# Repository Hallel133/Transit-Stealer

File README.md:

# Transit Stealer — V2

Open-hardware platform for **authorized NFC/RFID transit-card security research**: reading, analyzing, and interacting with transit fare cards for the purpose of testing and improving their security. This is not intended for, and must not be used for, unauthorized card cloning, skimming, or fare evasion.

## Board overview

V2 is a two-processor board:

- **RK3566** — main SoC (Cortex-A55 quad-core), running the host-side application. Referenced across three sheets since its pins are grouped by function (power, storage, RAM).
- **STM32G0B1CEUx** — dedicated MCU driving the NFC front end, largely independent of the RK3566 (own USB-C, own power sequencing), sharing only power/ground and a communication link with the rest of the board.
- **ST25R3911B-AQW** — NFC reader/writer IC, driven by the STM32G0 over SPI, feeding a custom hand-wound PCB loop antenna (see `Docs/Custom_Antenna.png`).
- **RK817-5 PMIC** — USB-C power in, battery charge/protection, all board rails (3.3V / 1.8V / DDR / CPU / GPU-NPU).
- **KLM8G1GETF-B041** eMMC and **D0811PM2FDGUK-U** LPDDR4 for RK3566 storage/RAM.
- **RTL8723BS** — WiFi/BT module (SDIO + UART).

Schematic is fully wired and ERC-clean (0 errors) as of this upload; PCB layout has not started.

## Repository layout

```
Hardware/
  Schematic/      V2 project + all hierarchical sheets (.kicad_sch/.kicad_pro/.kicad_prl), sym-lib-table
  PCB/            V2.kicad_pcb (layout, currently minimal/near-empty)
  Libraries/      Symbol libraries referenced by the schematic (bundled here so the project is self-contained)
Firmware/
  STM32G0_NFC_MCU/  Firmware for the NFC-side MCU (not started)
  RK3566_Host/      Host-side code for the RK3566 (not started)
Docs/
  Custom_Antenna.png  Hand-wound PCB loop antenna reference drawing
```

## Opening the project

1. Open `Hardware/Schematic/V2.kicad_pro` in KiCad 9.0.
2. The symbol libraries used by the LCD and eMMC parts live in `Hardware/Libraries/` and are referenced by `Hardware/Schematic/sym-lib-table` via relative (`${KIPRJMOD}`-based) paths, so the project should resolve them without any local path edits.
3. Run ERC (`kicad-cli sch erc` or the KiCad GUI) after any schematic change — sheets share nets, so the hierarchy is checked as one flat netlist.

## Status / next steps

- [x] Schematic: full net connectivity pass, power tree, decoupling, differential pairs verified
- [ ] PCB layout
- [ ] STM32G0 ↔ RK3566 communication firmware (next phase)

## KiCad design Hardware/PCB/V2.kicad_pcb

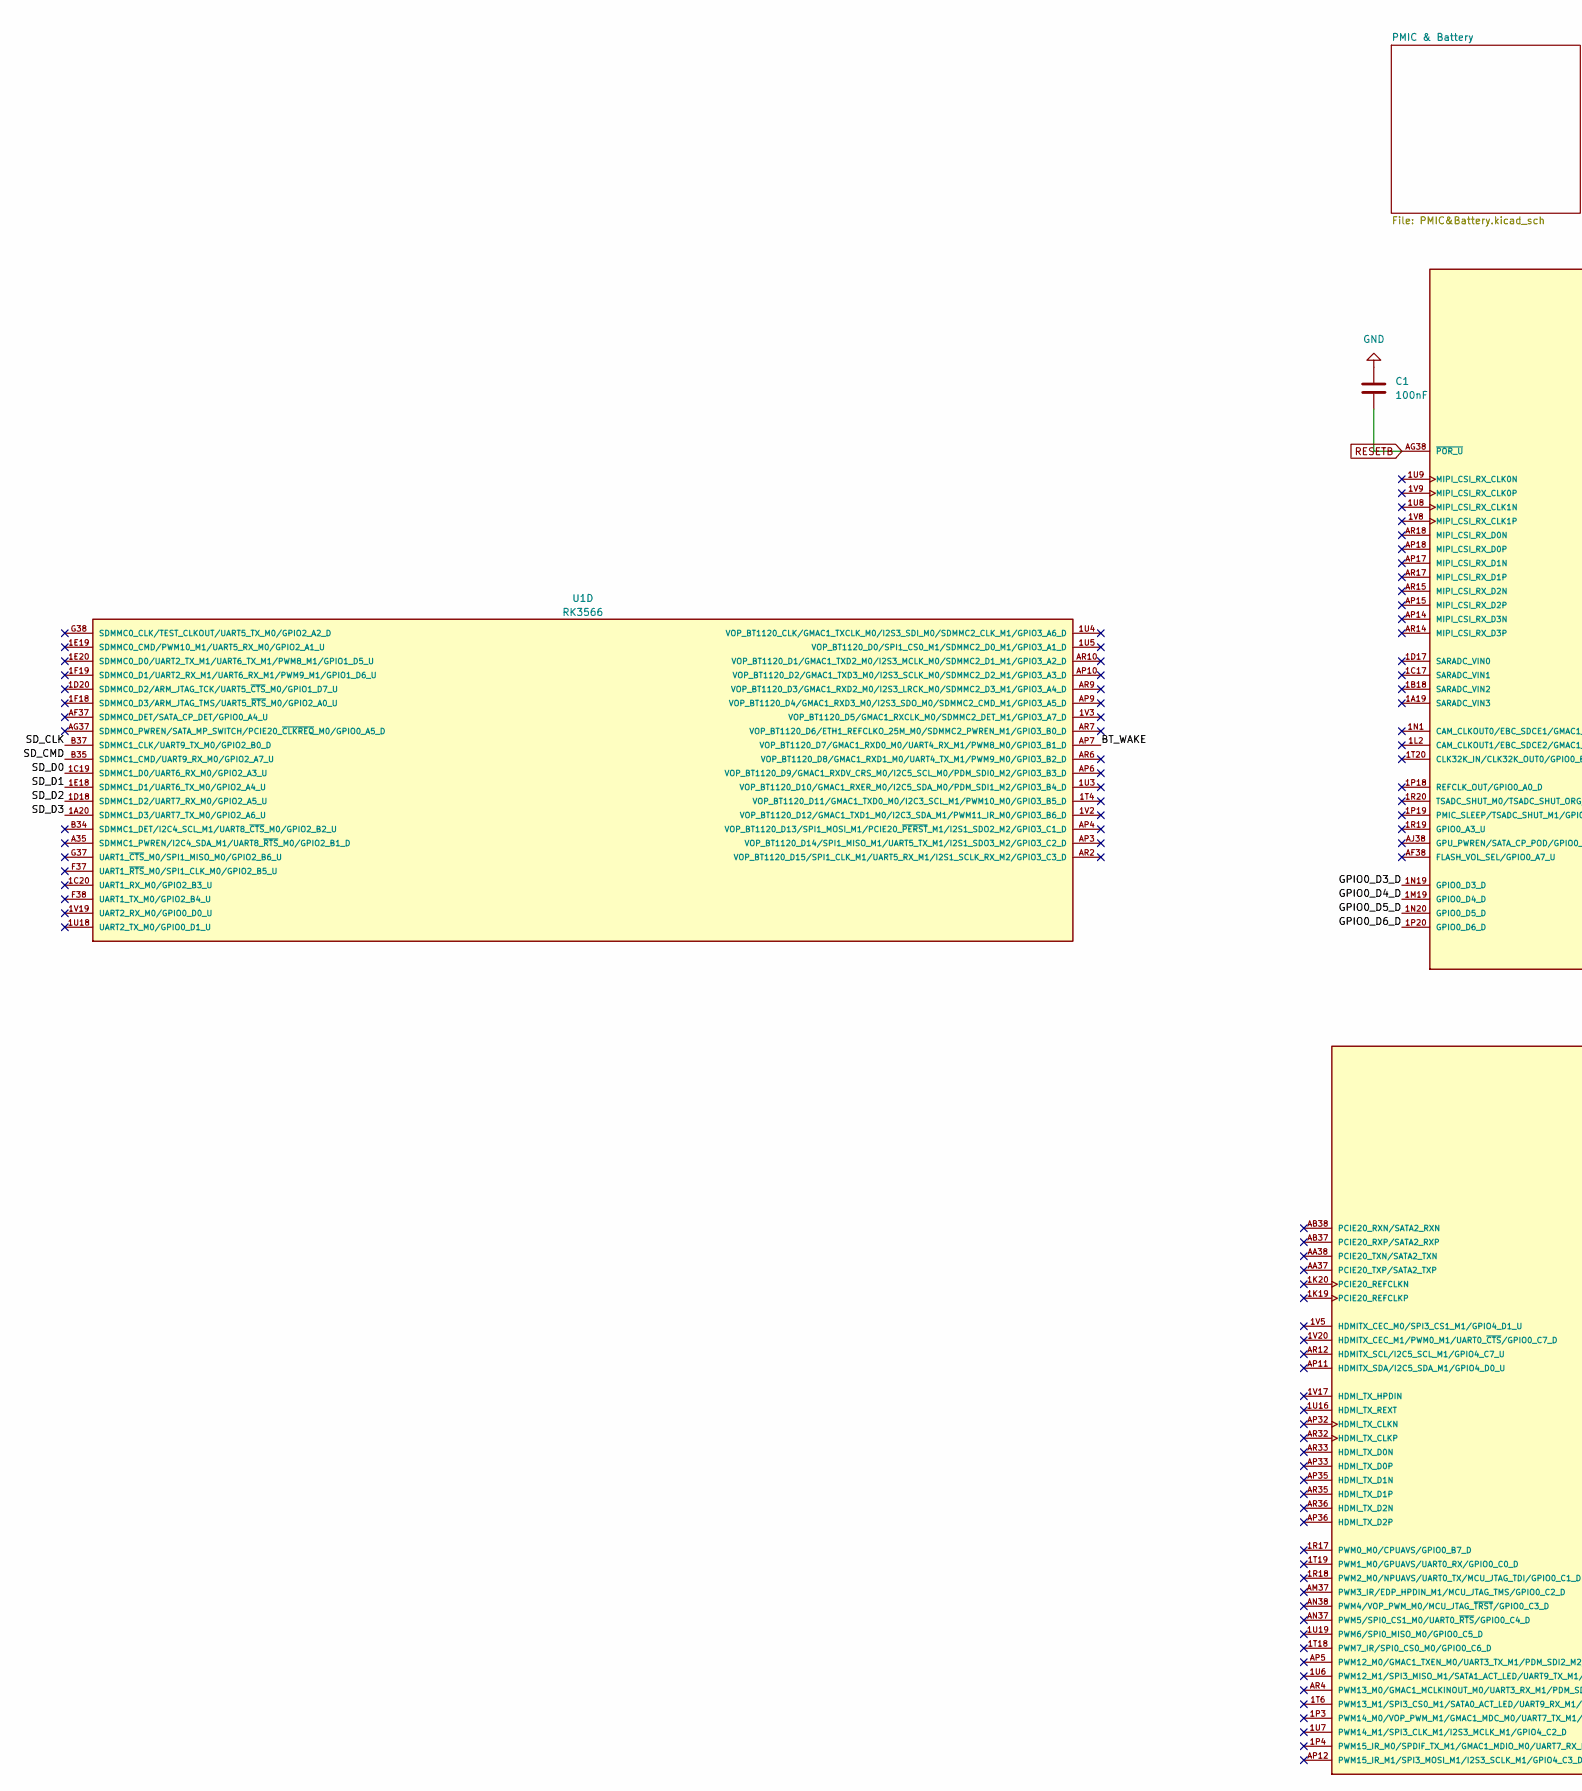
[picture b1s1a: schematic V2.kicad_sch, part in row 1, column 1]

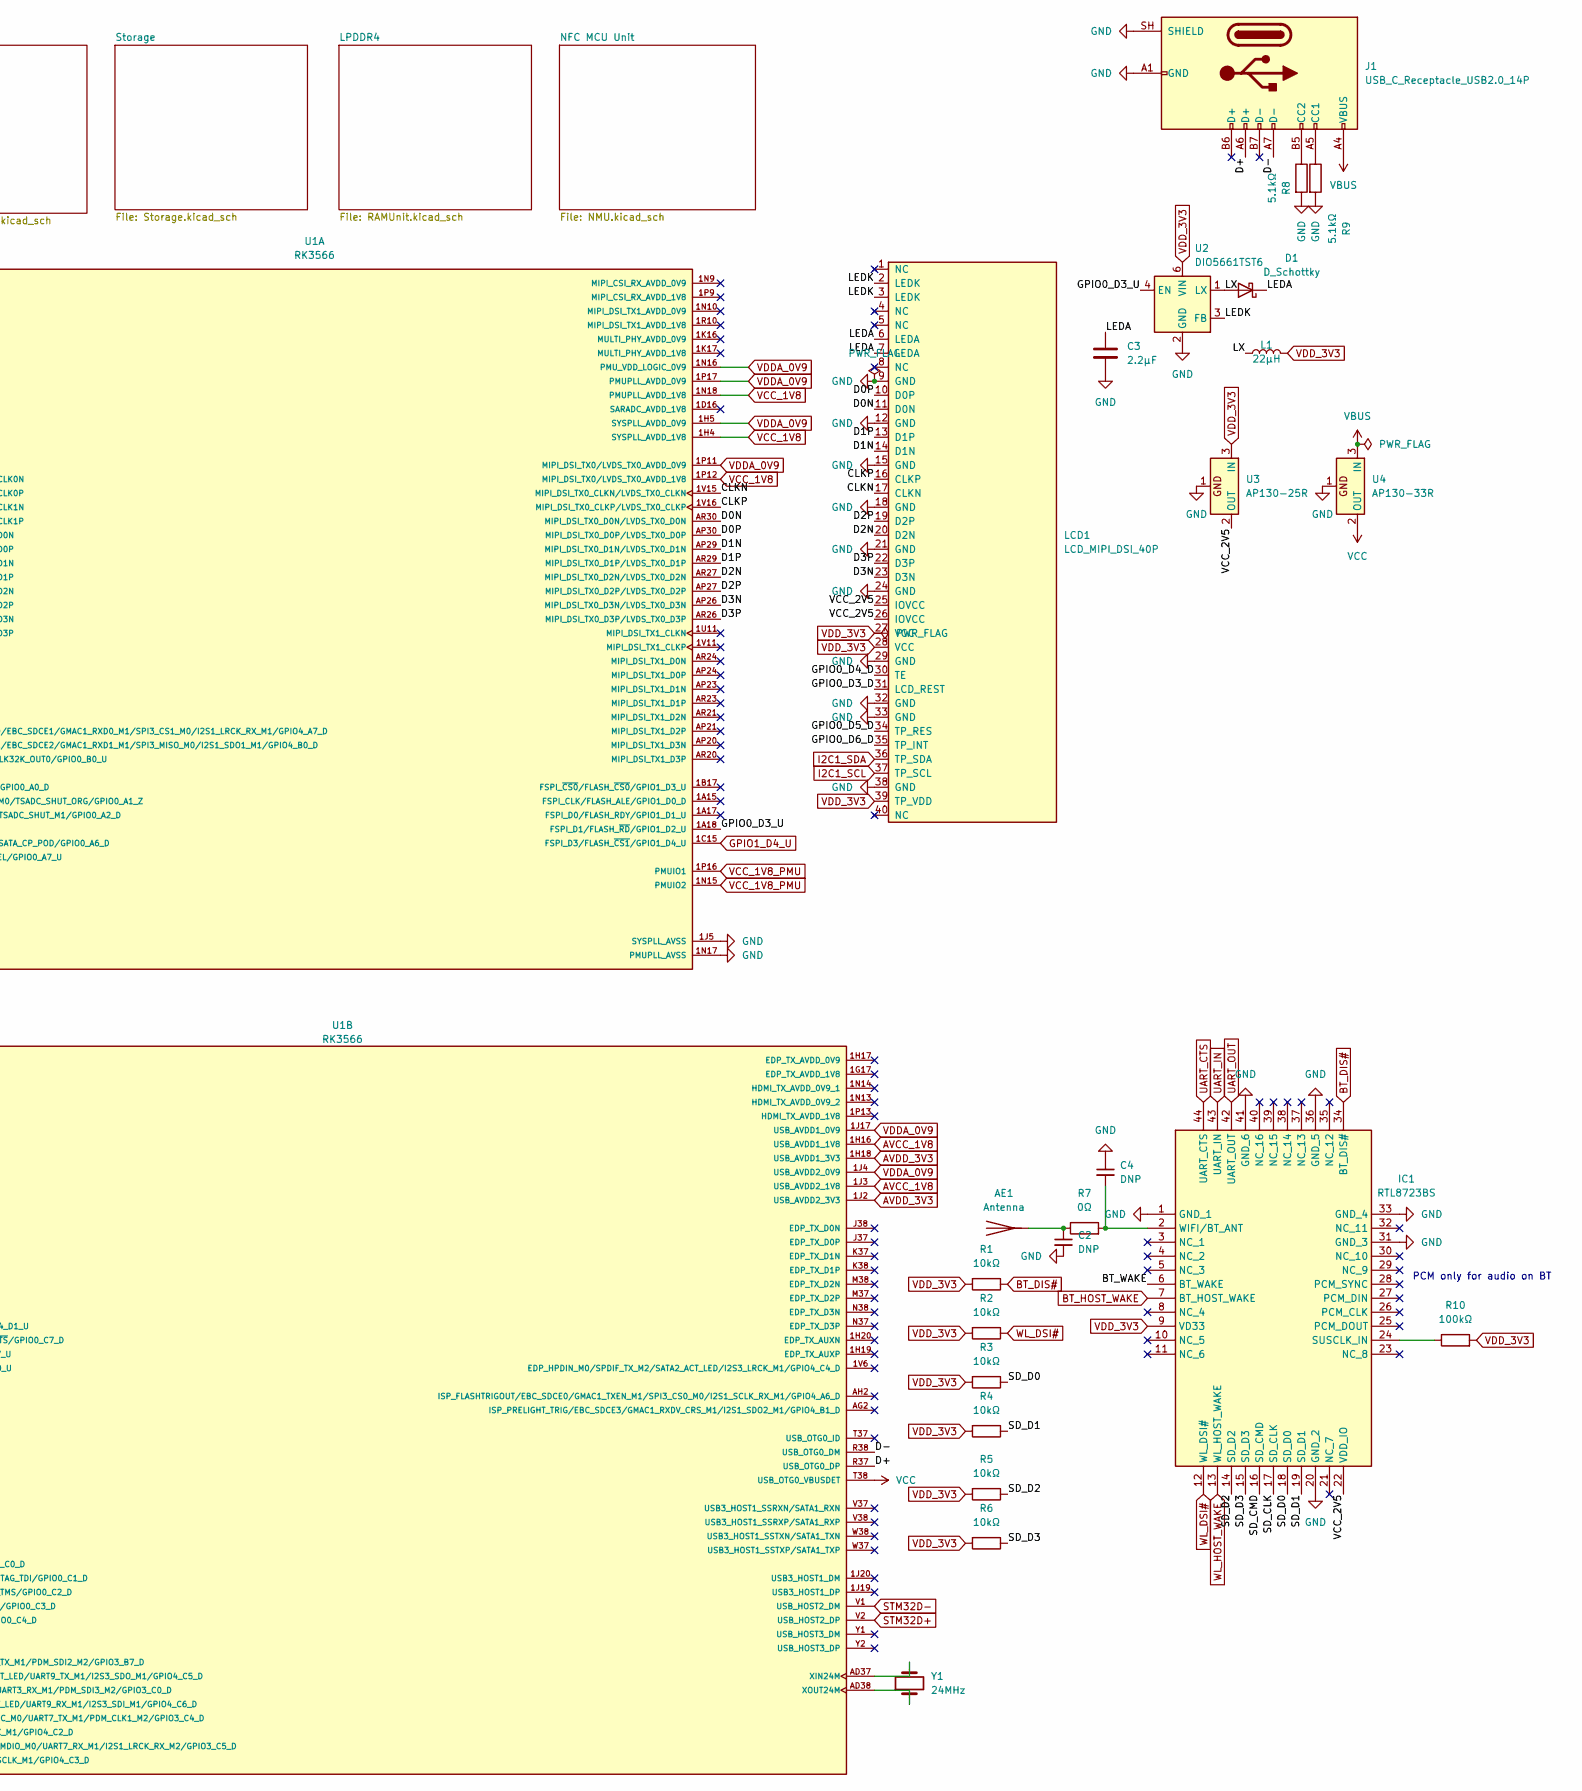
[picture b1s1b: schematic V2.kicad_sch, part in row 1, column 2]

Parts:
AE1: Antenna; Johanson_2450AT18x100
C1: 100nF; C_0402_1005Metric
C2, C4: DNP; C_0402_1005Metric
C3: 2.2µF; C_0402_1005Metric
D1: D_Schottky; D_SOD-123
IC1: RTL8723BS; Manufacturer_Part_Number RTL8723BS
J1: USB_C_Receptacle_USB2.0_14P; USB_C_Receptacle_GCT_USB4105-xx-A_16P_TopMnt_Horizontal
L1: 22µH; L_APV_ANR3010
LCD1: LCD_MIPI_DSI_40P; Amphenol_F32R-1A7x1-11040_1x40-1MP_P0.5mm_Horizontal
R1, R2, R3, R4, R5, R6: 10kΩ; R_0402_1005Metric
R7: 0Ω; R_0402_1005Metric
R8, R9: 5.1kΩ; R_0402_1005Metric
R10: 100kΩ; R_0402_1005Metric
U1: RK3566; PARTREV 1.1
U2: DIO5661TST6; TSOT-23-6
U3: AP130-25R; SC-59
U4: AP130-33R; SC-59
Y1: 24MHz; Crystal_SMD_3225-4Pin_3.2x2.5mm

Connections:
/BT_WAKE: IC1.6 (BT_WAKE), U1.AP7 (VOP_BT1120_D7/GMAC1_RXD0_M0/UART4_RX_M1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)
/CLKN: LCD1.17 (CLKN), U1.1V15 (MIPI_DSI_TX0_CLKN/LVDS_TX0_CLKN)
/CLKP: LCD1.16 (CLKP), U1.1V16 (MIPI_DSI_TX0_CLKP/LVDS_TX0_CLKP)
/D0N: LCD1.11 (D0N), U1.AR30 (MIPI_DSI_TX0_D0N/LVDS_TX0_D0N)
/D0P: LCD1.10 (D0P), U1.AP30 (MIPI_DSI_TX0_D0P/LVDS_TX0_D0P)
/D1N: LCD1.14 (D1N), U1.AP29 (MIPI_DSI_TX0_D1N/LVDS_TX0_D1N)
/D1P: LCD1.13 (D1P), U1.AR29 (MIPI_DSI_TX0_D1P/LVDS_TX0_D1P)
/D2N: LCD1.20 (D2N), U1.AR27 (MIPI_DSI_TX0_D2N/LVDS_TX0_D2N)
/D2P: LCD1.19 (D2P), U1.AP27 (MIPI_DSI_TX0_D2P/LVDS_TX0_D2P)
/D3N: LCD1.23 (D3N), U1.AP26 (MIPI_DSI_TX0_D3N/LVDS_TX0_D3N)
/D3P: LCD1.22 (D3P), U1.AR26 (MIPI_DSI_TX0_D3P/LVDS_TX0_D3P)
/D+: J1.A6 (D+), U1.R37 (USB_OTG0_DP)
/D-: J1.A7 (D-), U1.R38 (USB_OTG0_DM)
/GPIO0_D3_D: LCD1.31 (LCD_REST), U1.1N19 (GPIO0_D3_D)
/GPIO0_D3_U: U1.1A18 (FSPI_D1/FLASH_~RD/GPIO1_D2_U), U2.4 (EN)
/GPIO0_D4_D: LCD1.30 (TE), U1.1M19 (GPIO0_D4_D)
/GPIO0_D5_D: LCD1.34 (TP_RES), U1.1N20 (GPIO0_D5_D)
/GPIO0_D6_D: LCD1.35 (TP_INT), U1.1P20 (GPIO0_D6_D)
/LEDA: C3.1, D1.1 (K), LCD1.6 (LEDA), LCD1.7 (LEDA)
/LEDK: LCD1.2 (LEDK), LCD1.3 (LEDK), U2.3 (FB)
/LX: D1.2 (A), L1.1, U2.1 (LX)
/SD_CLK: IC1.17 (SD_CLK), U1.B37 (SDMMC1_CLK/UART9_TX_M0/GPIO2_B0_D)
/SD_CMD: IC1.16 (SD_CMD), U1.B35 (SDMMC1_CMD/UART9_RX_M0/GPIO2_A7_U)
/SD_D0: IC1.18 (SD_D0), R3.1, U1.1C19 (SDMMC1_D0/UART6_RX_M0/GPIO2_A3_U)
/SD_D1: IC1.19 (SD_D1), R4.1, U1.1E18 (SDMMC1_D1/UART6_TX_M0/GPIO2_A4_U)
/SD_D2: IC1.14 (SD_D2), R5.1, U1.1D18 (SDMMC1_D2/UART7_RX_M0/GPIO2_A5_U)
/SD_D3: IC1.15 (SD_D3), R6.1, U1.1A20 (SDMMC1_D3/UART7_TX_M0/GPIO2_A6_U)
/VCC_2V5: IC1.22 (VDD_IO), LCD1.25 (IOVCC), LCD1.26 (IOVCC), U3.2 (OUT)
AVCC_1V8: U1.1H16 (USB_AVDD1_1V8), U1.1J3 (USB_AVDD2_1V8); also elsewhere on the board
AVDD_3V3: U1.1H18 (USB_AVDD1_3V3), U1.1J2 (USB_AVDD2_3V3); also elsewhere on the board
BT_DIS#: IC1.34 (BT_DIS#), R1.1; also elsewhere on the board
BT_HOST_WAKE: IC1.7 (BT_HOST_WAKE); also elsewhere on the board
GND: C1.1, C2.2, C3.2, C4.1, IC1.1 (GND_1), IC1.20 (GND_2), IC1.31 (GND_3), IC1.33 (GND_4), IC1.36 (GND_5), IC1.41 (GND_6), J1.A1 (GND), J1.A12 (GND), J1.B1 (GND), J1.B12 (GND), J1.SH (SHIELD), LCD1.9 (GND), LCD1.12 (GND), LCD1.15 (GND), LCD1.18 (GND), LCD1.21 (GND), LCD1.24 (GND), LCD1.29 (GND), LCD1.32 (GND), LCD1.33 (GND), LCD1.38 (GND), R8.2, R9.2, U1.1J5 (SYSPLL_AVSS), U1.1N17 (PMUPLL_AVSS), U2.2 (GND), U3.1, U4.1; also elsewhere on the board
GPIO1_D4_U: U1.1C15 (FSPI_D3/FLASH_~CS1/GPIO1_D4_U); also elsewhere on the board
I2C1_SCL: LCD1.37 (TP_SCL); also elsewhere on the board
I2C1_SDA: LCD1.36 (TP_SDA); also elsewhere on the board
unnamed: AE1.1 (A_1), C2.1, R7.1
unnamed: IC1.24 (SUSCLK_IN), R10.1
unnamed: C4.2, IC1.2 (WIFI/BT_ANT), R7.2
unnamed: J1.A5 (CC1), R9.1
unnamed: J1.B5 (CC2), R8.1
unnamed: U1.AD37 (XIN24M), Y1.2
unnamed: U1.AD38 (XOUT24M), Y1.1
RESETB: C1.2, U1.AG38 (~POR_U); also elsewhere on the board
STM32D+: U1.V2 (USB_HOST2_DP); also elsewhere on the board
STM32D-: U1.V1 (USB_HOST2_DM); also elsewhere on the board
UART_CTS: IC1.44 (UART_CTS); also elsewhere on the board
UART_IN: IC1.43 (UART_IN); also elsewhere on the board
UART_OUT: IC1.42 (UART_OUT); also elsewhere on the board
VBUS: J1.A4 (VBUS), J1.A9 (VBUS), J1.B4 (VBUS), J1.B9 (VBUS), U4.3 (IN); also elsewhere on the board
VCC: U1.T38 (USB_OTG0_VBUSDET), U4.2 (OUT)
VCC_1V8: U1.1H4 (SYSPLL_AVDD_1V8), U1.1N18 (PMUPLL_AVDD_1V8), U1.1P12 (MIPI_DSI_TX0/LVDS_TX0_AVDD_1V8); also elsewhere on the board
VCC_1V8_PMU: U1.1N15 (PMUIO2), U1.1P16 (PMUIO1); also elsewhere on the board
VDDA_0V9: U1.1H5 (SYSPLL_AVDD_0V9), U1.1J4 (USB_AVDD2_0V9), U1.1J17 (USB_AVDD1_0V9), U1.1N16 (PMU_VDD_LOGIC_0V9), U1.1P11 (MIPI_DSI_TX0/LVDS_TX0_AVDD_0V9), U1.1P17 (PMUPLL_AVDD_0V9); also elsewhere on the board
VDD_3V3: IC1.9 (VD33), L1.2, LCD1.27 (VCC), LCD1.28 (VCC), LCD1.39 (TP_VDD), R1.2, R2.2, R3.2, R4.2, R5.2, R6.2, R10.2, U2.6 (VIN), U3.3 (IN); also elsewhere on the board
WL_DSI#: IC1.12 (WL_DSI#), R2.1; also elsewhere on the board
WL_HOST_WAKE: IC1.13 (WL_HOST_WAKE); also elsewhere on the board

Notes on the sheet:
PCM only for audio on BT

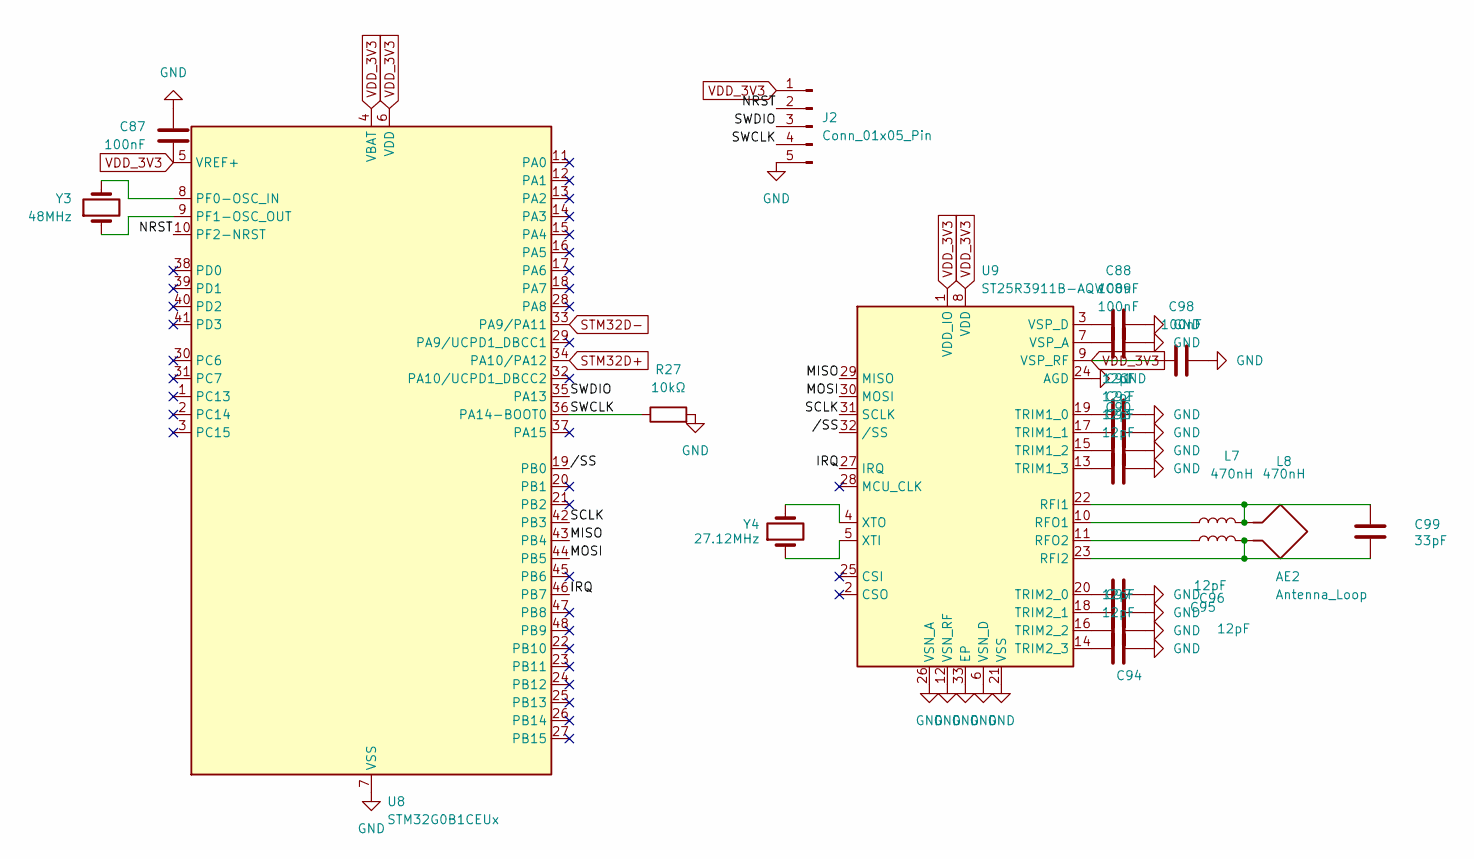
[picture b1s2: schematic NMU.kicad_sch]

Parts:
AE2: Antenna_Loop; TE_84952-4_1x04-1MP_P1.0mm_Horizontal
C87, C88, C89, C98: 100nF; C_0402_1005Metric
C90, C91, C92, C93, C94, C95, C96, C97: 12pF; C_0201_0603Metric
C99: 33pF; C_0201_0603Metric
J2: Conn_01x05_Pin; PinSocket_1x05_P1.00mm_Vertical_SMD_Pin1Left
L7, L8: 470nH; INDC2012X145N
R27: 10kΩ; R_0402_1005Metric
U8: STM32G0B1CEUx; QFN-48-1EP_7x7mm_P0.5mm_EP5.6x5.6mm
U9: ST25R3911B-AQW; VQFN-32-1EP_5x5mm_P0.5mm_EP3.5x3.5mm_ThermalVias
Y3: 48MHz; Crystal_SMD_3225-4Pin_3.2x2.5mm
Y4: 27.12MHz; Crystal_SMD_3225-4Pin_3.2x2.5mm

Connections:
/NFC MCU Unit/IRQ: U8.46 (PB7), U9.27 (IRQ)
/NFC MCU Unit/MISO: U8.43 (PB4), U9.29 (MISO)
/NFC MCU Unit/MOSI: U8.44 (PB5), U9.30 (MOSI)
/NFC MCU Unit/NRST: J2.2, U8.10 (PF2-NRST)
/NFC MCU Unit/SCLK: U8.42 (PB3), U9.31 (SCLK)
/NFC MCU Unit/SWCLK: J2.4, R27.1, U8.36 (PA14-BOOT0)
/NFC MCU Unit/SWDIO: J2.3, U8.35 (PA13)
/NFC MCU Unit//SS: U8.19 (PB0), U9.32 (/SS)
GND: C87.2, C88.2, C89.2, C90.1, C91.1, C92.1, C93.1, C94.1, C95.1, C96.1, C97.1, C98.2, J2.5, R27.2, U8.7 (VSS), U8.49 (VSS), U9.6 (VSN_D), U9.12 (VSN_RF), U9.21 (VSS), U9.24 (AGD), U9.26 (VSN_A), U9.33 (EP); also elsewhere on the board
unnamed: U8.8 (PF0-OSC_IN), Y3.2
unnamed: U8.9 (PF1-OSC_OUT), Y3.1
unnamed: AE2.1, C99.1, L7.2, U9.22 (RFI1)
unnamed: AE2.2, C99.2, L8.2, U9.23 (RFI2)
unnamed: L7.1, U9.10 (RFO1)
unnamed: L8.1, U9.11 (RFO2)
unnamed: C90.2, U9.19 (TRIM1_0)
unnamed: C91.2, U9.17 (TRIM1_1)
unnamed: C92.2, U9.15 (TRIM1_2)
unnamed: C93.2, U9.13 (TRIM1_3)
unnamed: C94.2, U9.20 (TRIM2_0)
unnamed: C95.2, U9.18 (TRIM2_1)
unnamed: C96.2, U9.16 (TRIM2_2)
unnamed: C97.2, U9.14 (TRIM2_3)
unnamed: C89.1, U9.7 (VSP_A)
unnamed: C88.1, U9.3 (VSP_D)
unnamed: U9.5 (XTI), Y4.1
unnamed: U9.4 (XTO), Y4.2
STM32D+: U8.34 (PA10/PA12); also elsewhere on the board
STM32D-: U8.33 (PA9/PA11); also elsewhere on the board
VDD_3V3: C87.1, C98.1, J2.1, U8.4 (VBAT), U8.5 (VREF+), U8.6 (VDD), U9.1 (VDD_IO), U9.8 (VDD), U9.9 (VSP_RF); also elsewhere on the board

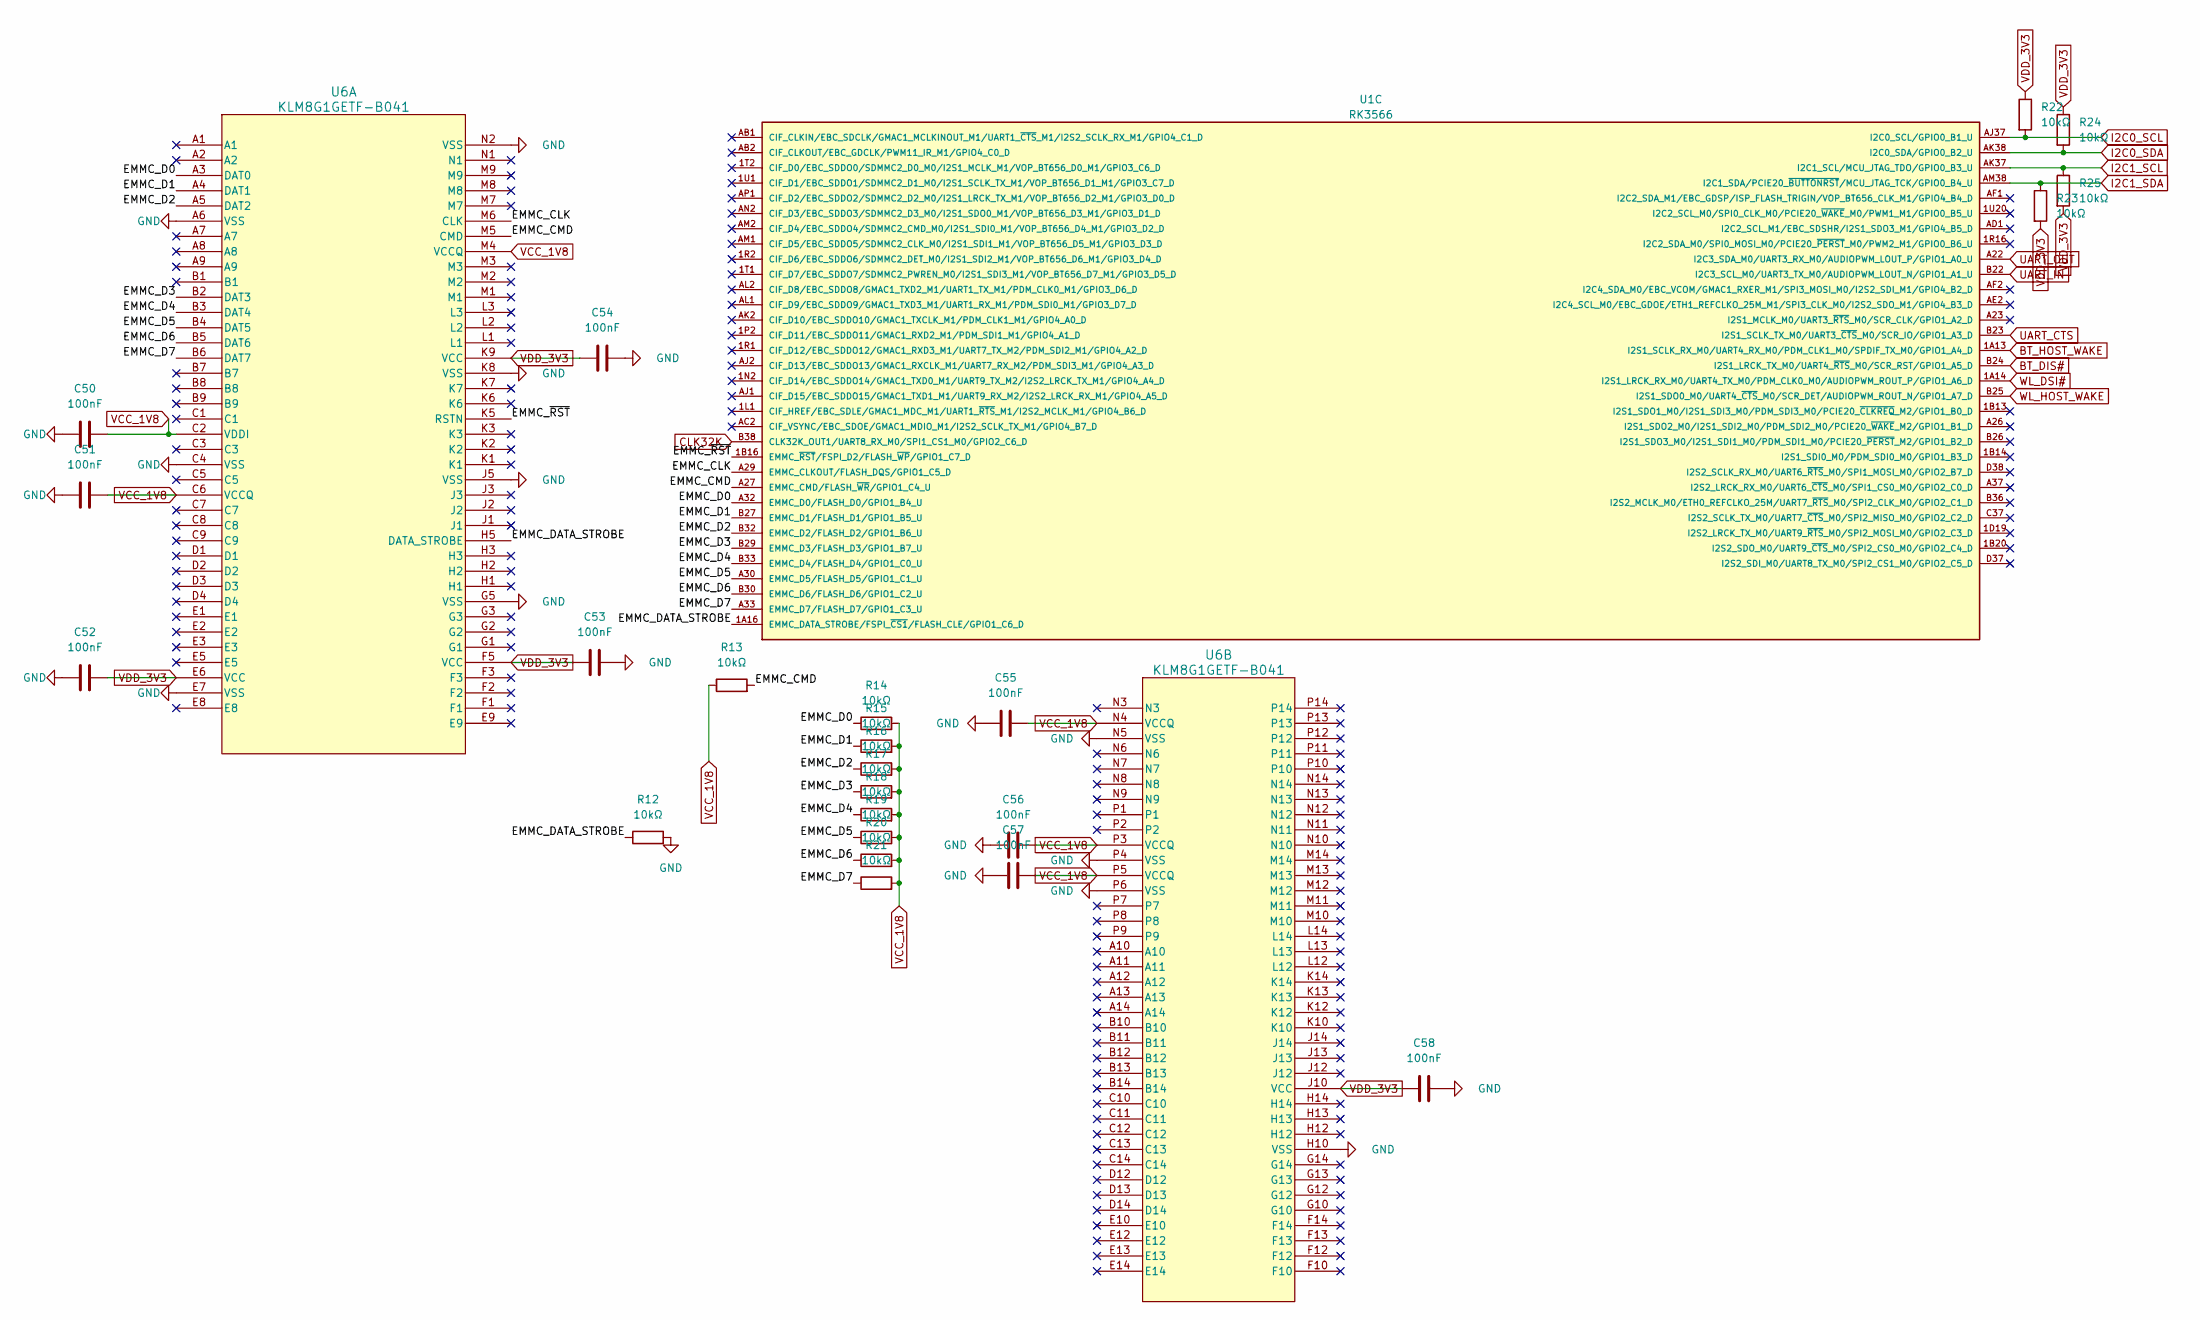
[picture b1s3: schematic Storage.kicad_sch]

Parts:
C50, C51, C52, C53, C54, C55, C56, C57, C58: 100nF; C_0402_1005Metric
R12, R13, R14, R15, R16, R17, R18, R19, R20, R21, R22, R23, R24, R25: 10kΩ; R_0402_1005Metric
U1: RK3566; PARTREV 1.1
U6: KLM8G1GETF-B041; KLMBG2JENB-B041_SAM-M

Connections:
/Storage/EMMC_CLK: U1.A29 (EMMC_CLKOUT/FLASH_DQS/GPIO1_C5_D), U6.M6 (CLK)
/Storage/EMMC_CMD: R13.2, U1.A27 (EMMC_CMD/FLASH_~WR/GPIO1_C4_U), U6.M5 (CMD)
/Storage/EMMC_D0: R14.1, U1.A32 (EMMC_D0/FLASH_D0/GPIO1_B4_U), U6.A3 (DAT0)
/Storage/EMMC_D1: R15.1, U1.B27 (EMMC_D1/FLASH_D1/GPIO1_B5_U), U6.A4 (DAT1)
/Storage/EMMC_D2: R16.1, U1.B32 (EMMC_D2/FLASH_D2/GPIO1_B6_U), U6.A5 (DAT2)
/Storage/EMMC_D3: R17.1, U1.B29 (EMMC_D3/FLASH_D3/GPIO1_B7_U), U6.B2 (DAT3)
/Storage/EMMC_D4: R18.1, U1.B33 (EMMC_D4/FLASH_D4/GPIO1_C0_U), U6.B3 (DAT4)
/Storage/EMMC_D5: R19.1, U1.A30 (EMMC_D5/FLASH_D5/GPIO1_C1_U), U6.B4 (DAT5)
/Storage/EMMC_D6: R20.1, U1.B30 (EMMC_D6/FLASH_D6/GPIO1_C2_U), U6.B5 (DAT6)
/Storage/EMMC_D7: R21.1, U1.A33 (EMMC_D7/FLASH_D7/GPIO1_C3_U), U6.B6 (DAT7)
/Storage/EMMC_DATA_STROBE: R12.1, U1.1A16 (EMMC_DATA_STROBE/FSPI_~CS1/FLASH_CLE/GP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), U6.H5 (DATA_STROBE)
/Storage/EMMC_~RST: U1.1B16 (EMMC_~RST/FSPI_D2/FLASH_~WP/GPIO1_C7_D), U6.K5 (RSTN)
BT_DIS#: U1.B24 (I2S1_LRCK_TX_M0/UART4_~RTS_M0/SCR_RST/G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); also elsewhere on the board
BT_HOST_WAKE: U1.1A13 (I2S1_SCLK_RX_M0/UART4_RX_M0/PDM_CLK1_M0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); also elsewhere on the board
CLK32K: U1.B38 (CLK32K_OUT1/UART8_RX_M0/SPI1_CS1_M0/GPI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); also elsewhere on the board
GND: C50.1, C51.1, C52.1, C53.2, C54.2, C55.1, C56.1, C57.1, C58.2, R12.2, U6.A6 (VSS), U6.C4 (VSS), U6.E7 (VSS), U6.G5 (VSS), U6.H10 (VSS), U6.J5 (VSS), U6.K8 (VSS), U6.N2 (VSS), U6.N5 (VSS), U6.P4 (VSS), U6.P6 (VSS); also elsewhere on the board
I2C0_SCL: R22.2, U1.AJ37 (I2C0_SCL/GPIO0_B1_U); also elsewhere on the board
I2C0_SDA: R24.2, U1.AK38 (I2C0_SDA/GPIO0_B2_U); also elsewhere on the board
I2C1_SCL: R25.1, U1.AK37 (I2C1_SCL/MCU_JTAG_TDO/GPIO0_B3_U); also elsewhere on the board
I2C1_SDA: R23.1, U1.AM38 (I2C1_SDA/PCIE20_~BUTTONRST/MCU_JTAG_TCK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); also elsewhere on the board
UART_CTS: U1.B23 (I2S1_SCLK_TX_M0/UART3_~CTS_M0/SCR_IO/GP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); also elsewhere on the board
UART_IN: U1.B22 (I2C3_SCL_M0/UART3_TX_M0/AUDIOPWM_LOUT_N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); also elsewhere on the board
UART_OUT: U1.A22 (I2C3_SDA_M0/UART3_RX_M0/AUDIOPWM_LOUT_P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); also elsewhere on the board
VCC_1V8: C50.2, C51.2, C55.2, C56.2, C57.2, R13.1, R14.2, R15.2, R16.2, R17.2, R18.2, R19.2, R20.2, R21.2, U6.C2 (VDDI), U6.C6 (VCCQ), U6.M4 (VCCQ), U6.N4 (VCCQ), U6.P3 (VCCQ), U6.P5 (VCCQ); also elsewhere on the board
VDD_3V3: C52.2, C53.1, C54.1, C58.1, R22.1, R23.2, R24.1, R25.2, U6.E6 (VCC), U6.F5 (VCC), U6.J10 (VCC), U6.K9 (VCC); also elsewhere on the board
WL_DSI#: U1.1A14 (I2S1_LRCK_RX_M0/UART4_TX_M0/PDM_CLK0_M0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); also elsewhere on the board
WL_HOST_WAKE: U1.B25 (I2S1_SDO0_M0/UART4_~CTS_M0/SCR_DET/AUDI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); also elsewhere on the board

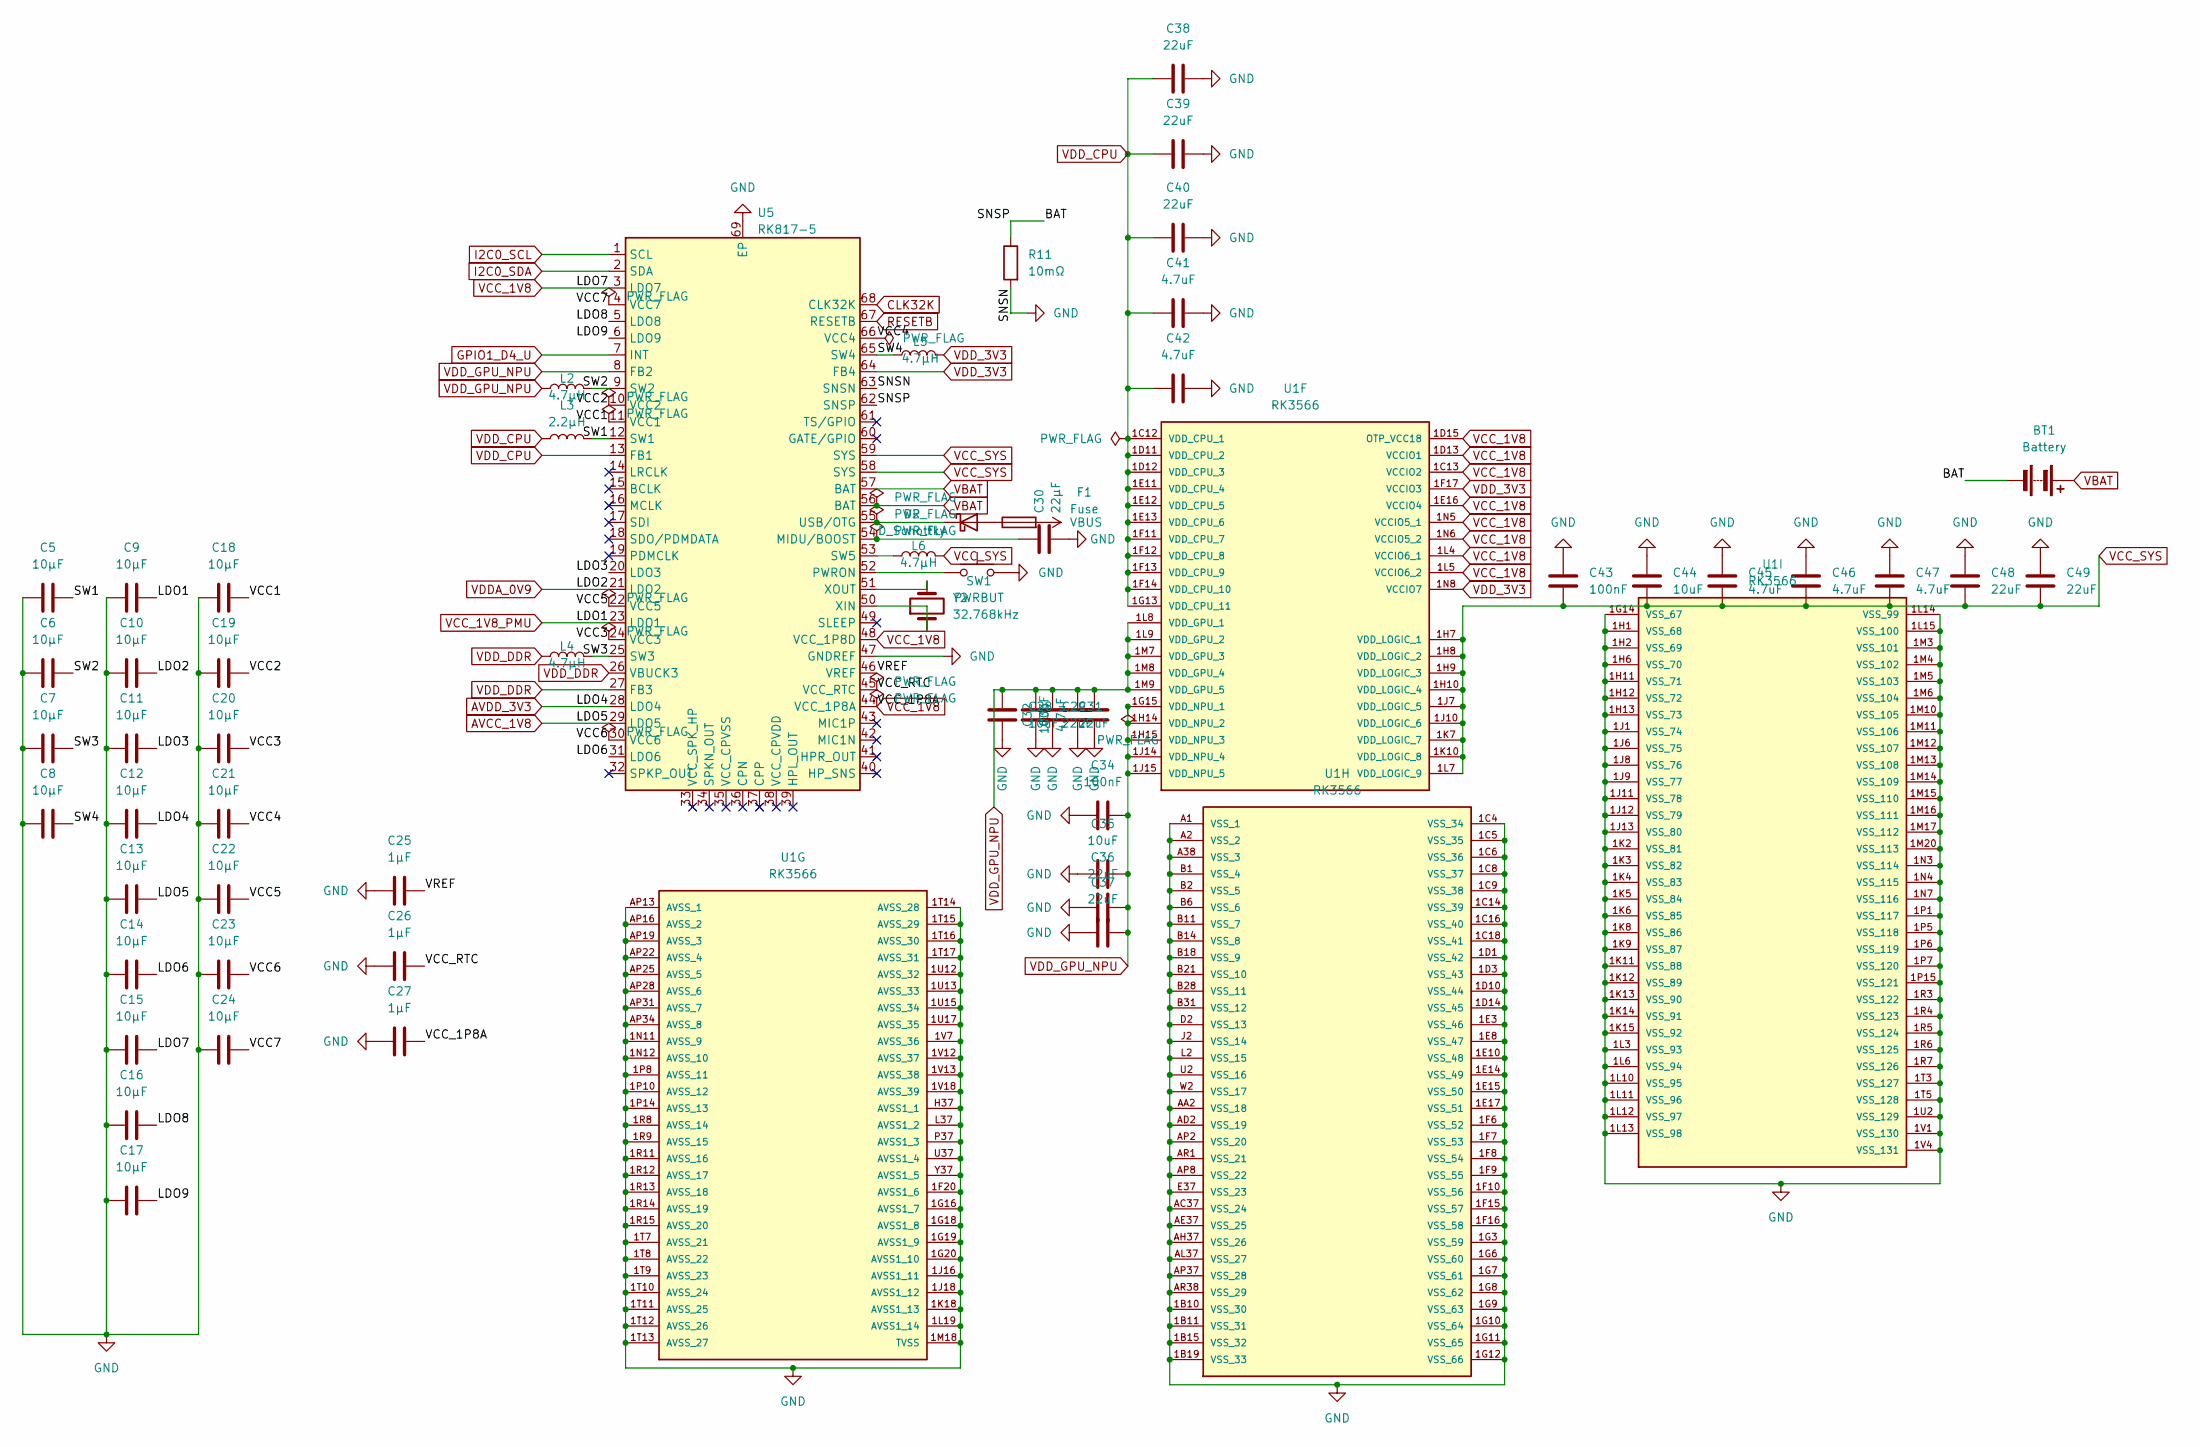
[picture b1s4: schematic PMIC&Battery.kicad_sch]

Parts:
BT1: Battery; SolderWire-0.127sqmm_1x02_P3.7mm_D0.48mm_OD1mm
C5, C6, C7, C8, C9, C10, C11, C12, C13, C14, C15, C16, C17, C18, C19, C20, C21, C22, C23, C24: 10µF; C_0402_1005Metric
C25, C26, C27: 1µF; C_0402_1005Metric
C28, C35, C44: 10uF; C_0402_1005Metric
C29, C31, C36, C37, C38, C39, C40, C48, C49: 22uF; C_0402_1005Metric
C30: 22µF; C_0402_1005Metric
C32, C34, C43: 100nF; C_0402_1005Metric
C33, C41, C42, C45, C46, C47: 4.7uF; C_0402_1005Metric
D2: D_Schottky; D_SMA
F1: Fuse; Fuse_0402_1005Metric
L2, L4, L5, L6: 4.7µH; L_APV_ANR3010
L3: 2.2µH; L_APV_ANR3010
R11: 10mΩ; R_1206_3216Metric
SW1: PWRBUT; SW_SPST_SKQG_WithStem
U1: RK3566; PARTREV 1.1
U5: RK817-5; QFN-68-1EP_8x8mm_P0.4mm_EP6.4x6.4mm_ThermalVias
Y2: 32.768kHz; Crystal_SMD_3215-2Pin_3.2x1.5mm

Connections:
/PMIC & Battery/BAT: BT1.2 (-), R11.1, U5.62 (SNSP)
/PMIC & Battery/LDO3: C11.2, U5.20 (LDO3)
/PMIC & Battery/LDO6: C14.2, U5.31 (LDO6)
/PMIC & Battery/LDO8: C16.2, U5.5 (LDO8)
/PMIC & Battery/LDO9: C17.2, U5.6 (LDO9)
/PMIC & Battery/SW1: C5.2, L3.2, U5.12 (SW1)
/PMIC & Battery/SW2: C6.2, L2.2, U5.9 (SW2)
/PMIC & Battery/SW3: C7.2, L4.2, U5.25 (SW3)
/PMIC & Battery/SW4: C8.1, L5.1, U5.65 (SW4)
/PMIC & Battery/VCC1: C18.2, U5.11 (VCC1)
/PMIC & Battery/VCC2: C19.2, U5.10 (VCC2)
/PMIC & Battery/VCC3: C20.2, U5.24 (VCC3)
/PMIC & Battery/VCC4: C21.2, U5.66 (VCC4)
/PMIC & Battery/VCC5: C22.2, U5.22 (VCC5)
/PMIC & Battery/VCC6: C23.2, U5.30 (VCC6)
/PMIC & Battery/VCC7: C24.2, U5.4 (VCC7)
/PMIC & Battery/VCC_RTC: C26.1, U5.45 (VCC_RTC)
/PMIC & Battery/VREF: C25.1, U5.46 (VREF)
AVCC_1V8: C13.2, U5.29 (LDO5); also elsewhere on the board
AVDD_3V3: C12.2, U5.28 (LDO4); also elsewhere on the board
CLK32K: U5.68 (CLK32K); also elsewhere on the board
GND: C5.1, C6.1, C7.1, C8.2, C9.1, C10.1, C11.1, C12.1, C13.1, C14.1, C15.1, C16.1, C17.1, C18.1, C19.1, C20.1, C21.1, C22.1, C23.1, C24.1, C25.2, C26.2, C27.2, C28.2, C29.2, C30.2, C31.2, C32.2, C33.2, C34.2, C35.2, C36.2, C37.2, C38.2, C39.2, C40.2, C41.2, C42.2, C43.1, C44.1, C45.1, C46.1, C47.1, C48.1, C49.1, R11.2, SW1.2, U1.1B10 (VSS_30), U1.1B11 (VSS_31), U1.1B15 (VSS_32), U1.1B19 (VSS_33), U1.1C4 (VSS_34), U1.1C5 (VSS_35), U1.1C6 (VSS_36), U1.1C8 (VSS_37), U1.1C9 (VSS_38), U1.1C14 (VSS_39), U1.1C16 (VSS_40), U1.1C18 (VSS_41), U1.1D1 (VSS_42), U1.1D3 (VSS_43), U1.1D10 (VSS_44), U1.1D14 (VSS_45), U1.1E3 (VSS_46), U1.1E8 (VSS_47), U1.1E10 (VSS_48), U1.1E14 (VSS_49), U1.1E15 (VSS_50), U1.1E17 (VSS_51), U1.1F6 (VSS_52), U1.1F7 (VSS_53), U1.1F8 (VSS_54), U1.1F9 (VSS_55), U1.1F10 (VSS_56), U1.1F15 (VSS_57), U1.1F16 (VSS_58), U1.1F20 (AVSS1_6), U1.1G3 (VSS_59), U1.1G6 (VSS_60), U1.1G7 (VSS_61), U1.1G8 (VSS_62), U1.1G9 (VSS_63), U1.1G10 (VSS_64), U1.1G11 (VSS_65), U1.1G12 (VSS_66), U1.1G14 (VSS_67), U1.1G16 (AVSS1_7), U1.1G18 (AVSS1_8), U1.1G19 (AVSS1_9), U1.1G20 (AVSS1_10), U1.1H1 (VSS_68), U1.1H2 (VSS_69), U1.1H6 (VSS_70), U1.1H11 (VSS_71), U1.1H12 (VSS_72), U1.1H13 (VSS_73), U1.1J1 (VSS_74), U1.1J6 (VSS_75), U1.1J8 (VSS_76), U1.1J9 (VSS_77), U1.1J11 (VSS_78), U1.1J12 (VSS_79), U1.1J13 (VSS_80), U1.1J16 (AVSS1_11), U1.1J18 (AVSS1_12), U1.1K2 (VSS_81), U1.1K3 (VSS_82), U1.1K4 (VSS_83), U1.1K5 (VSS_84), U1.1K6 (VSS_85), U1.1K8 (VSS_86), U1.1K9 (VSS_87), U1.1K11 (VSS_88), U1.1K12 (VSS_89), U1.1K13 (VSS_90), U1.1K14 (VSS_91), U1.1K15 (VSS_92), U1.1K18 (AVSS1_13), U1.1L3 (VSS_93), U1.1L6 (VSS_94), U1.1L10 (VSS_95), U1.1L11 (VSS_96), U1.1L12 (VSS_97), U1.1L13 (VSS_98), U1.1L14 (VSS_99), U1.1L15 (VSS_100), U1.1L19 (AVSS1_14), U1.1M3 (VSS_101), U1.1M4 (VSS_102), U1.1M5 (VSS_103), U1.1M6 (VSS_104), U1.1M10 (VSS_105), U1.1M11 (VSS_106), U1.1M12 (VSS_107), U1.1M13 (VSS_108), U1.1M14 (VSS_109), U1.1M15 (VSS_110), U1.1M16 (VSS_111), U1.1M17 (VSS_112), U1.1M18 (TVSS), U1.1M20 (VSS_113), U1.1N3 (VSS_114), U1.1N4 (VSS_115), U1.1N7 (VSS_116), U1.1N11 (AVSS_9), U1.1N12 (AVSS_10), U1.1P1 (VSS_117), U1.1P5 (VSS_118), U1.1P6 (VSS_119), U1.1P7 (VSS_120), U1.1P8 (AVSS_11), U1.1P10 (AVSS_12), U1.1P14 (AVSS_13), U1.1P15 (VSS_121), U1.1R3 (VSS_122), U1.1R4 (VSS_123), U1.1R5 (VSS_124), U1.1R6 (VSS_125), U1.1R7 (VSS_126), U1.1R8 (AVSS_14), U1.1R9 (AVSS_15), U1.1R11 (AVSS_16), U1.1R12 (AVSS_17), U1.1R13 (AVSS_18), U1.1R14 (AVSS_19), U1.1R15 (AVSS_20), U1.1T3 (VSS_127), U1.1T5 (VSS_128), U1.1T7 (AVSS_21), U1.1T8 (AVSS_22), U1.1T9 (AVSS_23), U1.1T10 (AVSS_24), U1.1T11 (AVSS_25), U1.1T12 (AVSS_26), U1.1T13 (AVSS_27), U1.1T14 (AVSS_28), U1.1T15 (AVSS_29), U1.1T16 (AVSS_30), U1.1T17 (AVSS_31), U1.1U2 (VSS_129), U1.1U12 (AVSS_32), U1.1U13 (AVSS_33), U1.1U15 (AVSS_34), U1.1U17 (AVSS_35), U1.1V1 (VSS_130), U1.1V4 (VSS_131), U1.1V7 (AVSS_36), U1.1V12 (AVSS_37), U1.1V13 (AVSS_38), U1.1V18 (AVSS_39), U1.A1 (VSS_1), U1.A2 (VSS_2), U1.A38 (VSS_3), U1.AA2 (VSS_18), U1.AC37 (VSS_24), U1.AD2 (VSS_19), U1.AE37 (VSS_25), U1.AH37 (VSS_26), U1.AL37 (VSS_27), U1.AP2 (VSS_20), U1.AP8 (VSS_22), U1.AP13 (AVSS_1), U1.AP16 (AVSS_2), U1.AP19 (AVSS_3), U1.AP22 (AVSS_4), U1.AP25 (AVSS_5), U1.AP28 (AVSS_6), U1.AP31 (AVSS_7), U1.AP34 (AVSS_8)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; also elsewhere on the board
GPIO1_D4_U: U5.7 (INT); also elsewhere on the board
I2C0_SCL: U5.1 (SCL); also elsewhere on the board
I2C0_SDA: U5.2 (SDA); also elsewhere on the board
unnamed: D2.2 (A), F1.1
unnamed: D2.1 (K), U5.55 (USB/OTG)
unnamed: C30.1, U5.54 (MIDU/BOOST)
unnamed: SW1.1, U5.52 (PWRON)
unnamed: L6.1, U5.53 (SW5)
unnamed: U5.50 (XIN), Y2.1
unnamed: U5.51 (XOUT), Y2.2
RESETB: U5.67 (RESETB); also elsewhere on the board
VBAT: BT1.1 (+), U5.56 (BAT), U5.57 (BAT)
VBUS: F1.2; also elsewhere on the board
VCC_1V8: C15.2, C27.1, U1.1C13 (VCCIO2), U1.1D13 (VCCIO1), U1.1D15 (OTP_VCC18), U1.1E16 (VCCIO4), U1.1L4 (VCCIO6_1), U1.1L5 (VCCIO6_2), U1.1N5 (VCCIO5_1), U1.1N6 (VCCIO5_2), U5.3 (LDO7), U5.44 (VCC_1P8A), U5.48 (VCC_1P8D); also elsewhere on the board
VCC_1V8_PMU: C9.2, U5.23 (LDO1); also elsewhere on the board
VCC_SYS: C43.2, C44.2, C45.2, C46.2, C47.2, C48.2, C49.2, L6.2, U1.1H7 (VDD_LOGIC_1), U1.1H8 (VDD_LOGIC_2), U1.1H9 (VDD_LOGIC_3), U1.1H10 (VDD_LOGIC_4), U1.1J7 (VDD_LOGIC_5), U1.1J10 (VDD_LOGIC_6), U1.1K7 (VDD_LOGIC_7), U1.1K10 (VDD_LOGIC_8), U1.1L7 (VDD_LOGIC_9), U5.58 (SYS), U5.59 (SYS)
VDDA_0V9: C10.2, U5.21 (LDO2); also elsewhere on the board
VDD_3V3: L5.2, U1.1F17 (VCCIO3), U1.1N8 (VCCIO7), U5.64 (FB4); also elsewhere on the board
VDD_CPU: C38.1, C39.1, C40.1, C41.1, C42.1, L3.1, U1.1C12 (VDD_CPU_1), U1.1D11 (VDD_CPU_2), U1.1D12 (VDD_CPU_3), U1.1E11 (VDD_CPU_4), U1.1E12 (VDD_CPU_5), U1.1E13 (VDD_CPU_6), U1.1F11 (VDD_CPU_7), U1.1F12 (VDD_CPU_8), U1.1F13 (VDD_CPU_9), U1.1F14 (VDD_CPU_10), U1.1G13 (VDD_CPU_11), U5.13 (FB1)
VDD_DDR: L4.1, U5.26 (VBUCK3), U5.27 (FB3); also elsewhere on the board
VDD_GPU_NPU: C28.1, C29.1, C31.1, C32.1, C33.1, C34.1, C35.1, C36.1, C37.1, L2.1, U1.1G15 (VDD_NPU_1), U1.1H14 (VDD_NPU_2), U1.1H15 (VDD_NPU_3), U1.1J14 (VDD_NPU_4), U1.1J15 (VDD_NPU_5), U1.1L8 (VDD_GPU_1), U1.1L9 (VDD_GPU_2), U1.1M7 (VDD_GPU_3), U1.1M8 (VDD_GPU_4), U1.1M9 (VDD_GPU_5), U5.8 (FB2)
